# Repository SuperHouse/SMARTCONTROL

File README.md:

Home Automation Smart Switch Controller
=======================================
Copyright 2017-2018 SuperHouse Automation Pty Ltd <www.superhouse.tv>  

Control board for home automation switches. Mounts on the back of an
illuminated button breakout, and connects to a central controller via
wires or WiFi.

Features:

 * ESP8266 with WiFi
 * RJ45 breakout to allow connecting using Cat-5 cable

More information is available at:

  http://www.superhouse.tv/smartcontrol

INSTALLATION
------------
The design is saved as an EAGLE project. EAGLE PCB design software is
available from www.cadsoftusa.com free for non-commercial use. To use
this project download it and place the directory containing these files
into the "eagle" directory on your computer. Then open EAGLE and
navigate to the project.

DISTRIBUTION
------------
The specific terms of distribution of this project are governed by the
license referenced below.

LICENSE
-------
Licensed under the TAPR Open Hardware License (www.tapr.org/OHL).
The "license" folder within this repository also contains a copy of
this license in plain text format.

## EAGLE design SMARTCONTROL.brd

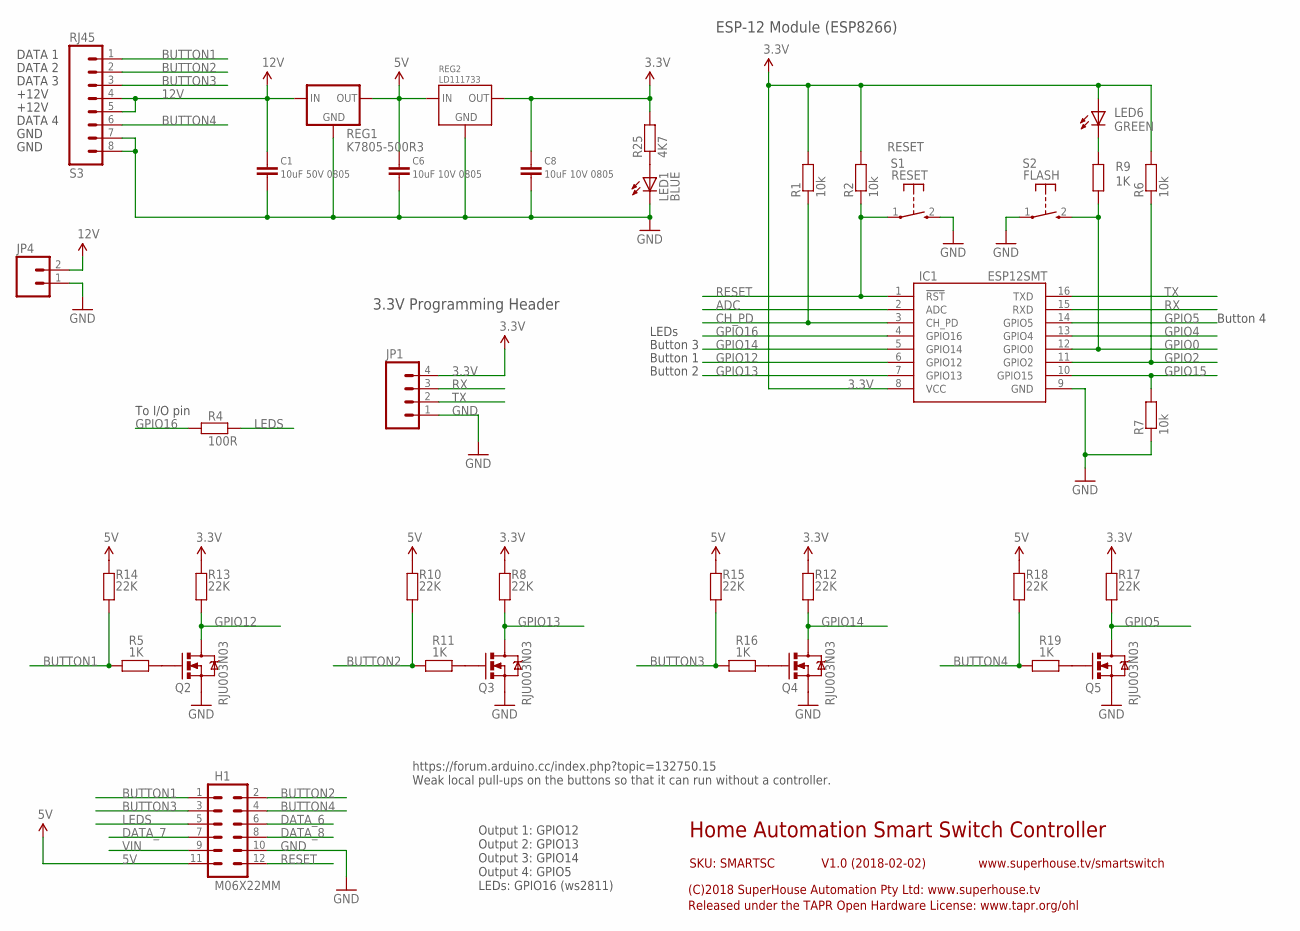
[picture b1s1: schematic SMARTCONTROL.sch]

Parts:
C1: 10uF 50V 0805; C0805
C6, C8: 10uF 10V 0805; C0805
H1: M06X22MM; 2X6-2MM
IC1: ESP12SMT; ESP12
JP1: M04PTH; 1X04
JP4: M023.5MM; SCREWTERMINAL-3.5MM-2
LED1: BLUE; LED-0603
LED6: GREEN; LED-0603
Q2, Q3, Q4, Q5: RJU003N03; SOT32-3
R1, R2, R6, R7: 10k; 0603
R4: 100R; 0603
R5, R9, R11, R16, R19: 1K; 0603
R8, R10, R12, R13, R14, R15, R17, R18: 22K; 0603
R25: 4K7; 0603
REG1: K7805-500R3; K78XX-500R3
REG2: LD111733; SOT-223
S1: RESET; TACTILE_SWITCH_SMD_2PIN_TINY
S2: FLASH; TACTILE_SWITCH_SMD_2PIN_TINY
S3: RJ45

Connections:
3.3V: C8.1, IC1.8 (VCC), JP1.4, LED6.A, R1.2, R2.2, R6.2, R8.2, R12.2, R13.2, R17.2, R25.2, REG2.2 (OUT), REG2.4 (OUT)
5V: C6.1, H1.11, R10.2, R14.2, R15.2, R18.2, REG1.3 (OUT), REG2.3 (IN)
12V: C1.1, JP4.2, REG1.1 (IN), S3.4, S3.5
ADC: IC1.2 (ADC)
BUTTON1: H1.1, R5.2, R14.1, S3.1
BUTTON2: H1.2, R10.1, R11.2, S3.2
BUTTON3: H1.3, R15.1, R16.2, S3.3
BUTTON4: H1.4, R18.1, R19.2, S3.6
CH_PD: IC1.3 (CH_PD), R1.1
DATA_6: H1.6
DATA_7: H1.7
DATA_8: H1.8
GND: C1.2, C6.2, C8.2, H1.10, IC1.9 (GND), JP1.1, JP4.1, LED1.C, Q2.2 (S), Q3.2 (S), Q4.2 (S), Q5.2 (S), R7.1, REG1.2 (GND), REG2.1 (GND), S1.2 (S), S2.1, S3.7, S3.8
GPIO0: IC1.12 (GPIO0), R9.2, S2.2 (S)
GPIO2: IC1.11 (GPIO2), R6.1
GPIO4: IC1.13 (GPIO4)
GPIO5: IC1.14 (GPIO5), Q5.3 (D), R17.1
GPIO12: IC1.6 (GPIO12), Q2.3 (D), R13.1
GPIO13: IC1.7 (GPIO13), Q3.3 (D), R8.1
GPIO14: IC1.5 (GPIO14), Q4.3 (D), R12.1
GPIO15: IC1.10 (GPIO15), R7.2
GPIO16: IC1.4 (GPIO16), R4.2
LEDS: H1.5, R4.1
unnamed: Q2.1 (G), R5.1
unnamed: Q3.1 (G), R11.1
unnamed: Q4.1 (G), R16.1
unnamed: Q5.1 (G), R19.1
unnamed: LED1.A, R25.1
unnamed: LED6.C, R9.1
RESET: H1.12, IC1.1 (!RST), R2.1, S1.1
RX: IC1.15 (RXD), JP1.3
TX: IC1.16 (TXD), JP1.2
VIN: H1.9

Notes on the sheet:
Home Automation Smart Switch Controller
V1.0 (2018-02-02)
SKU: SMARTSC
(C)2018 SuperHouse Automation Pty Ltd: www.superhouse.tv
Released under the TAPR Open Hardware License: www.tapr.org/ohl
www.superhouse.tv/smartswitch
https://forum.arduino.cc/index.php?topic=132750.15 Weak local pull-ups on the buttons so that it can run without a controller.
ESP-12 Module (ESP8266)
Output 1: GPIO12 Output 2: GPIO13 Output 3: GPIO14 Output 4: GPIO5 LEDs: GPIO16 (ws2811)
3.3V Programming Header
DATA 1
DATA 2
DATA 3
DATA 4
+12V
GND
To I/O pin
Button 1
Button 2
Button 3
Button 4
LEDs

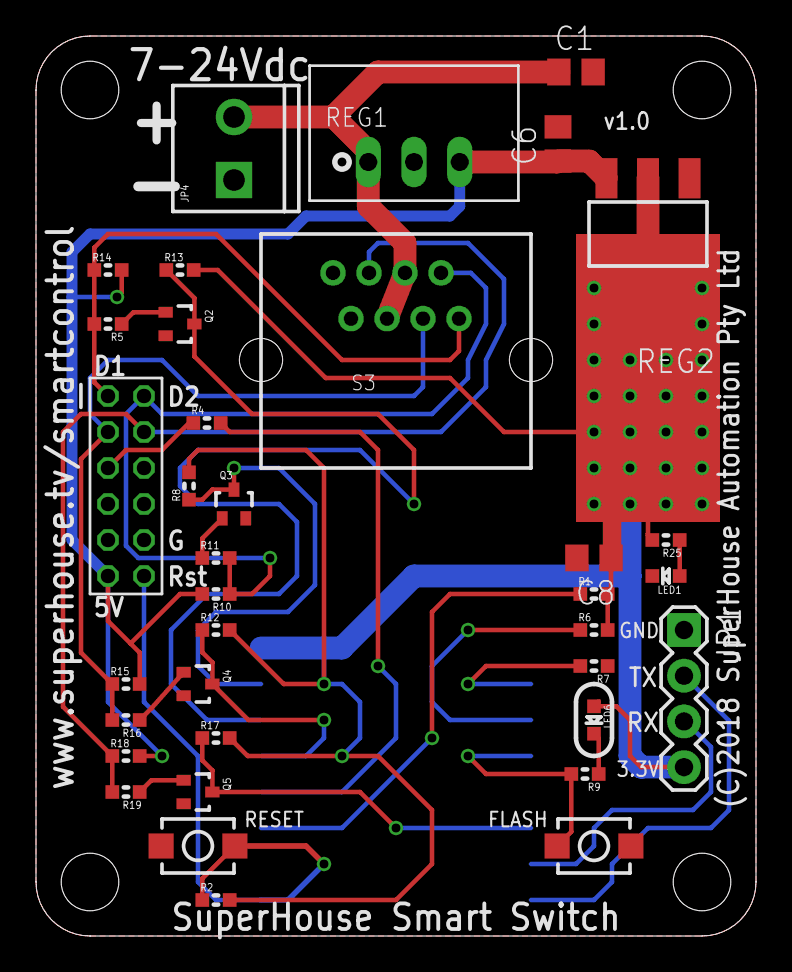
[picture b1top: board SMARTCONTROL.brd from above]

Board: 2 copper layers, 40.0 x 50.0 mm, 37 parts (1 on the bottom side), 27 nets.

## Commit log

2018-04-11 Re-import of project developed over the last 9 months
2018-04-11 Fixed ESP-12 footprint (swapped D4/5)
2019-07-01 Replaced most parts using SuperHouse library to add 3D models
